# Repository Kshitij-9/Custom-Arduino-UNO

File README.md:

# Custom-Arduino-UNO
#Software - Autodesk EAGLE

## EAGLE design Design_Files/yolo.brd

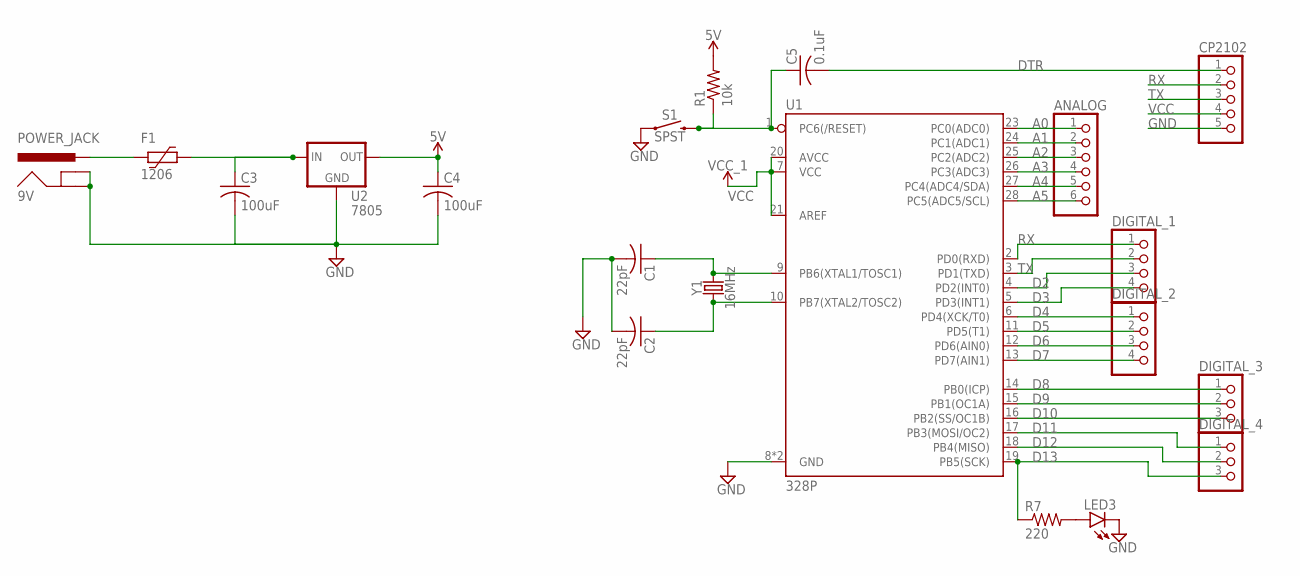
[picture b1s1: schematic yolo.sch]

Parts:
9V: POWER_JACK; POWER_JACK_PTH
ANALOG: PINHD-1X6; 1X06
C1, C2: 22pF; C025-025X050
C3, C4: 100uF; C025-025X050
C5: 0.1uF; C025-025X050
CP2102: PINHD-1X5; 1X05
DIGITAL_1, DIGITAL_2: PINHD-1X4; 1X04
DIGITAL_3, DIGITAL_4: PINHD-1X3; 1X03
F1: 1206; 1206L
LED3: LED5MM
R1: 10k; 0204/7
R7: 220; 0204/7
S1: SPST; TACTILE_SWITCH_PTH_6.0MM
U1: 328P; DIP28
U2: 7805; DC-DC_CONVERTER_78XX
Y1: 16MHz; HC49US

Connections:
A0: ANALOG.1, U1.23 (PC0(ADC0))
A1: ANALOG.2, U1.24 (PC1(ADC1))
A2: ANALOG.3, U1.25 (PC2(ADC2))
A3: ANALOG.4, U1.26 (PC3(ADC3))
A4: ANALOG.5, U1.27 (PC4(ADC4/SDA))
A5: ANALOG.6, U1.28 (PC5(ADC5/SCL))
D2: DIGITAL_1.3, U1.4 (PD2(INT0))
D3: DIGITAL_1.4, U1.5 (PD3(INT1))
D4: DIGITAL_2.1, U1.6 (PD4(XCK/T0))
D5: DIGITAL_2.2, U1.11 (PD5(T1))
D6: DIGITAL_2.3, U1.12 (PD6(AIN0))
D7: DIGITAL_2.4, U1.13 (PD7(AIN1))
D8: DIGITAL_3.1, U1.14 (PB0(ICP))
D9: DIGITAL_3.2, U1.15 (PB1(OC1A))
D10: DIGITAL_3.3, U1.16 (PB2(SS/OC1B))
D11: DIGITAL_4.1, U1.17 (PB3(MOSI/OC2))
D12: DIGITAL_4.2, U1.18 (PB4(MISO))
D13: DIGITAL_4.3, R7.1, U1.19 (PB5(SCK))
DTR: C5.2, CP2102.1
GND: 9V.GND, 9V.GNDBREAK, C1.2, C2.2, C3.2, C4.2, CP2102.5, LED3.K (C), S1.1, U1.8 (GND), U1.22 (GND), U2.GND
unnamed: 9V.PWR, F1.2
unnamed: C3.1, F1.1, U2.VIN (IN)
unnamed: C1.1, U1.9 (PB6(XTAL1/TOSC1)), Y1.2
unnamed: C2.1, U1.10 (PB7(XTAL2/TOSC2)), Y1.1
unnamed: LED3.A, R7.2
RST: C5.1, R1.1, S1.3 (2), U1.1 (PC6(/RESET))
RX: CP2102.2, DIGITAL_1.1, U1.2 (PD0(RXD))
TX: CP2102.3, DIGITAL_1.2, U1.3 (PD1(TXD))
VCC: CP2102.4, U1.7 (VCC), U1.20 (AVCC), U1.21 (AREF)
VCC_1: C4.1, R1.2, U2.VOUT (OUT)

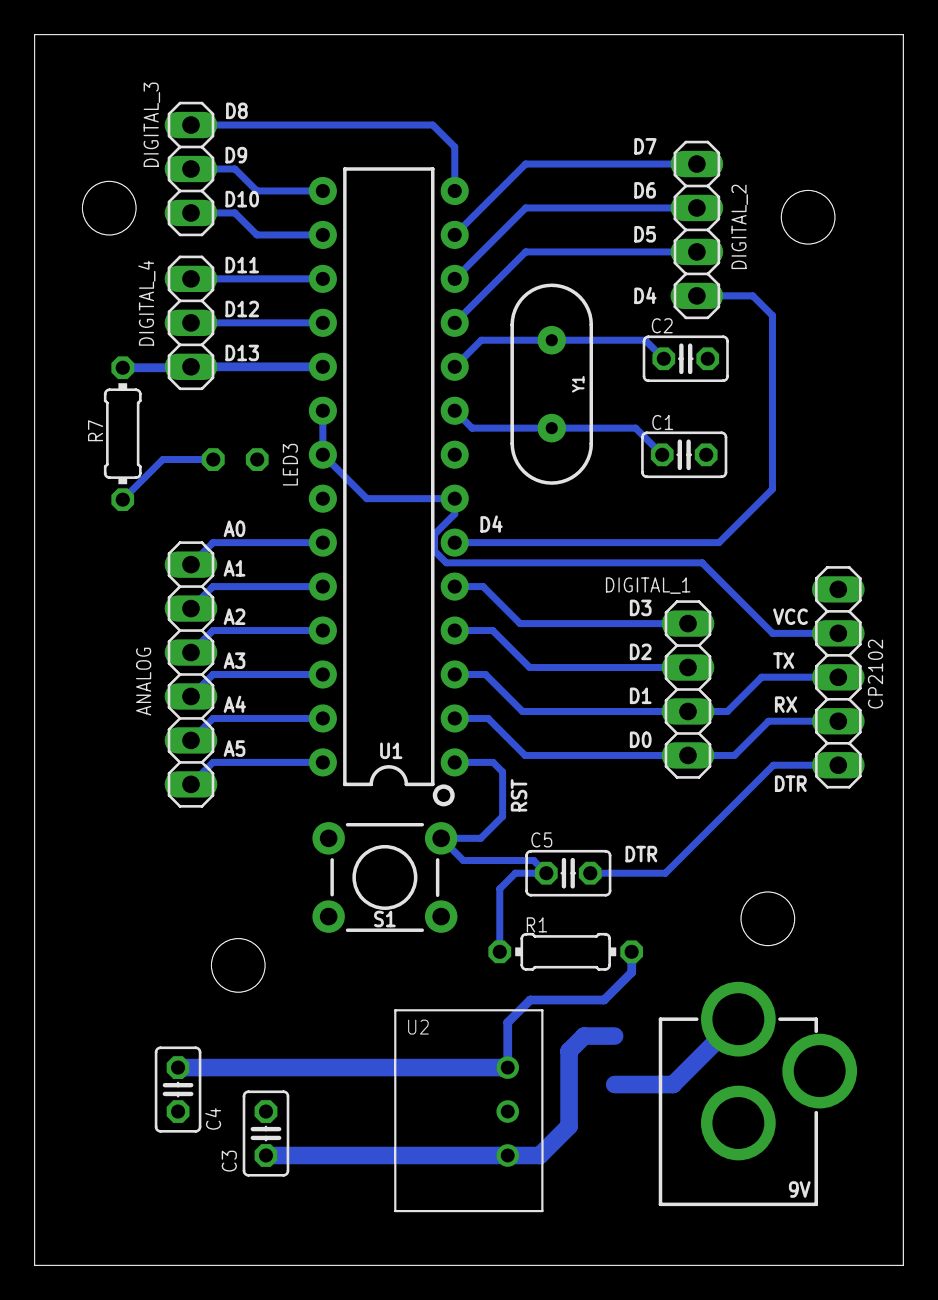
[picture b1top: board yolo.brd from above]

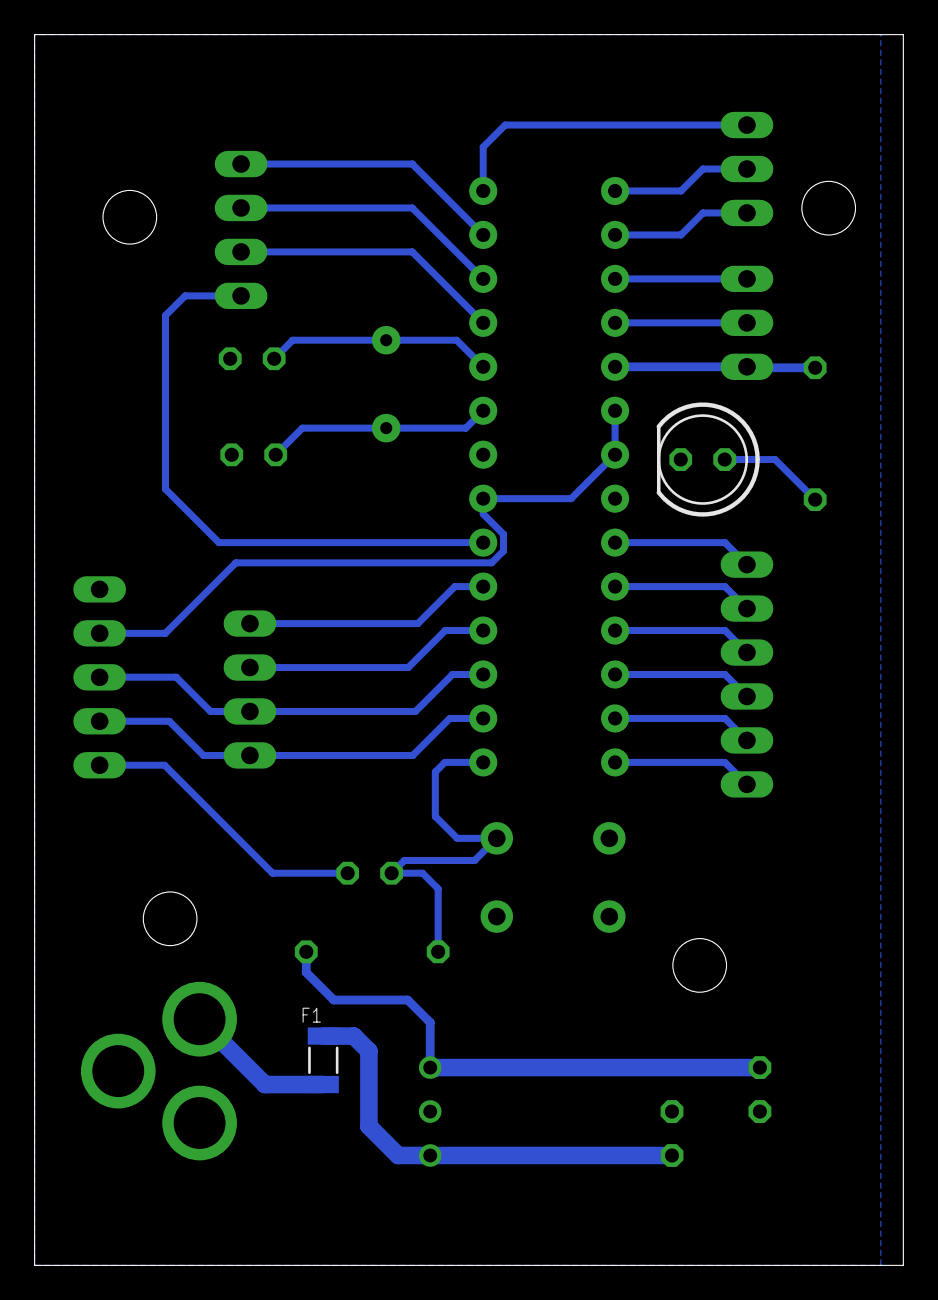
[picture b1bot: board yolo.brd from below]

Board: 2 copper layers, 50.2 x 71.1 mm, 20 parts (2 on the bottom side), 30 nets.

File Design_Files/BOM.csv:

"Qty";"Value";"Device";"Package";"Parts";"Description";"";
"1";"";"LED5MM";"LED5MM";"LED3";"LED";"";
"2";"";"PINHD-1X3";"1X03";"DIGITAL_3, DIGITAL_4";"PIN HEADER";"";
"2";"";"PINHD-1X4";"1X04";"DIGITAL_1, DIGITAL_2";"PIN HEADER";"";
"1";"";"PINHD-1X5";"1X05";"CP2102";"PIN HEADER";"";
"1";"";"PINHD-1X6";"1X06";"ANALOG";"PIN HEADER";"";
"1";"0.1uF";"C-US025-025X050";"C025-025X050";"C5";"CAPACITOR, American symbol";"";
"2";"100uF";"C-US025-025X050";"C025-025X050";"C3, C4";"CAPACITOR, American symbol";"";
"1";"10k";"R-US_0204/7";"0204/7";"R1";"RESISTOR, American symbol";"";
"1";"1206";"1206L175SL";"1206L";"F1";"Polyfuse Resettable PTC";"";
"1";"16MHz";"CRYSTAL-16MHZPTH-HC49US";"HC49US";"Y1";"16MHz Crystal";"";
"1";"220";"R-US_0204/7";"0204/7";"R7";"RESISTOR, American symbol";"";
"2";"22pF";"C-US025-025X050";"C025-025X050";"C1, C2";"CAPACITOR, American symbol";"";
"1";"328P";"ATMEGA328P_PDIP";"DIP28";"U1";"Atmel 328P";"";
"1";"7805";"R-78E5.0-1.0";"DC-DC_CONVERTER_78XX";"U2";"Recom Power 5V 1A DC/DC Converter";"";
"1";"POWER_JACK";"POWER_JACK";"POWER_JACK_PTH";"9V";"Power Jack Connector";"";
"1";"SPST";"MOMENTARY-SWITCH-SPST-PTH-6.0MM";"TACTILE_SWITCH_PTH_6.0MM";"S1";"Momentary Switch (Pushbutton) - SPST";"";

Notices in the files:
parts and their libraries:
SparkFun-Connectors: Licensing: Creative Commons ShareAlike 4.0 International - https://creativecommons.org/licenses/by-sa/4.0
